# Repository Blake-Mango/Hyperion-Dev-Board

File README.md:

# Hyperion-Dev-Board

s a simple dev board that I made for Hack Club Blueprint. It has everything that I would want on a dev board—lots of GPIOs, plenty of grounds, and some other useful features (listed below). This was a fun and pretty easy project to make once I started to understand what I needed to do. It ended up being foundational to my ability to design PCBs, and it showed me how much I enjoy this kind of work. I hope I’ll be able to make even more dev boards later in life, and I’m definitely planning to try some other PCB ideas on Blueprint soon.

# Features
1. The RP2040 is the brain of this project handling all of the processing
2. this uses the W25Q16JVZPIQ with a whopping 16-Megabit flash menmory
3. Usbc this is just a normal USB-C Receptical to send data and also power 
4. one pin for 5v power and another pin for 3v power 
5. 9 pins for ground to make it easy to ground everything you need to 
6. this board comes wih 29 gpio pins 4 of which are dual use for analog inputs (ADC pins)
7. also on this board is an led to make it easy to check if the board is powered on od if there any any problems also to help debug or even program
8. and finaly a button to enter into BOOTSEL mode so you can program you board.

# schematic

# PCB Layout
### Front:

### Back:

# Heres what it looks like when made

# Demo
here is a short code that was made to just rotate the color of the onboard neopixel led

https://github.com/user-attachments/assets/beb6644e-a9f9-4d21-ad0d-ccec5cd91aba

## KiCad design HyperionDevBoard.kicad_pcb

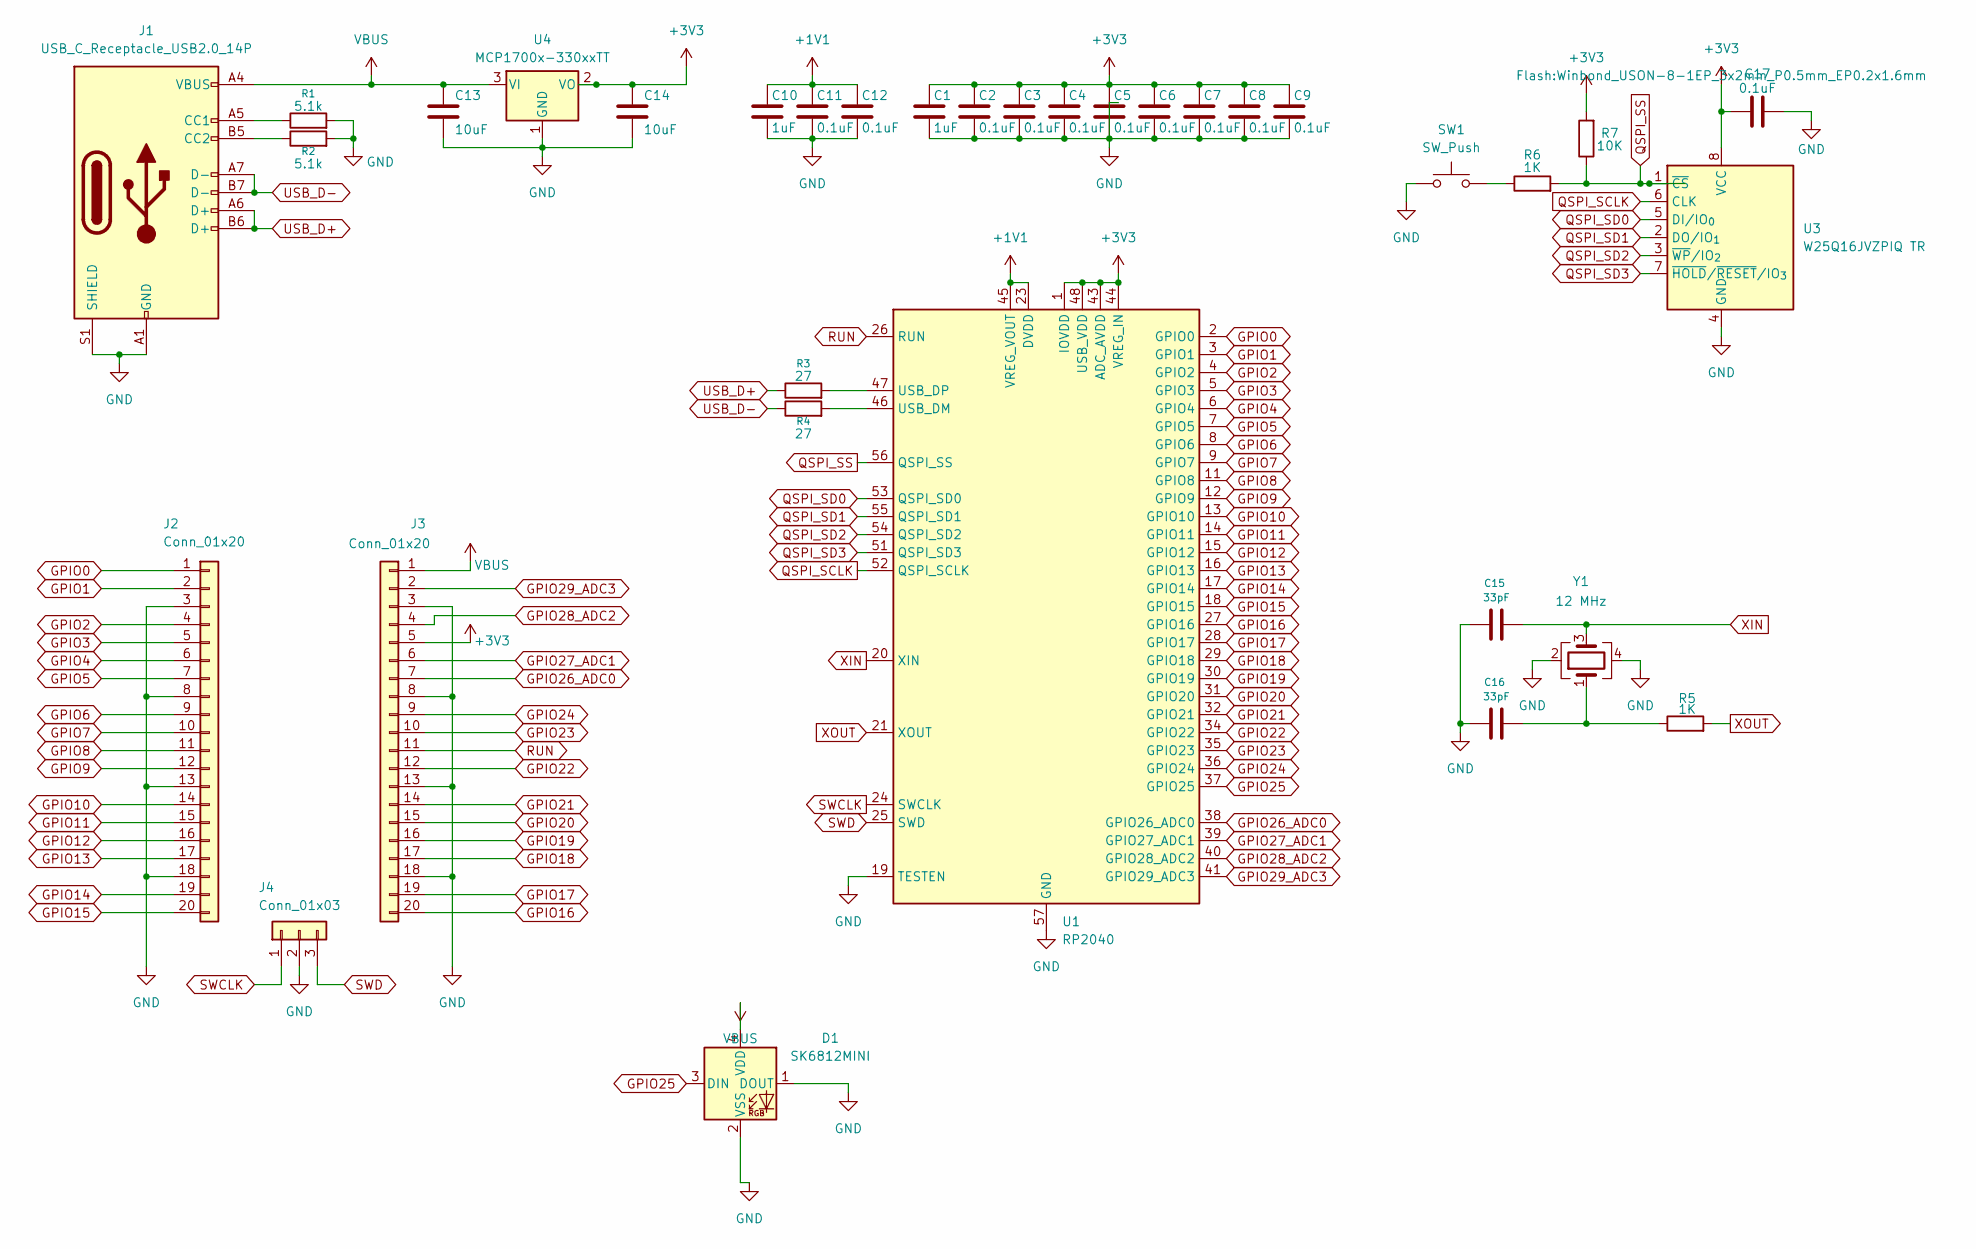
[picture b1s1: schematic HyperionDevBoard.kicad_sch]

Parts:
C1, C10: 1uF; C_0402_1005Metric
C2, C3, C4, C5, C6, C7, C8, C9, C11, C12, C17: 0.1uF; C_0402_1005Metric
C13, C14: 10uF; C_0603_1608Metric
C15, C16: 33pF; C_0402_1005Metric
D1: SK6812MINI; MX_SK6812MINI-E
J1: USB_C_Receptacle_USB2.0_14P; USB_C_Receptacle_HRO_TYPE-C-31-M-12
J2, J3: Conn_01x20; PinHeader_1x20_P2.54mm_Vertical
J4: Conn_01x03; PinHeader_1x03_P2.54mm_Vertical
R1, R2: 5.1k; R_0402_1005Metric
R3, R4: 27; R_0402_1005Metric
R5, R6: 1K; R_0402_1005Metric
R7: 10K; R_0402_1005Metric
SW1: SW_Push; SW_Push_SPST_NO_Alps_SKRK
U1: RP2040; QFN-56-1EP_7x7mm_P0.4mm_EP3.2x3.2mm
U3: W25Q16JVZPIQ TR; Winbond_USON-8-1EP_3x2mm_P0.5mm_EP0.2x1.6mm
U4: MCP1700x-330xxTT; SOT-23
Y1: 12 MHz; Crystal_SMD_3225-4Pin_3.2x2.5mm

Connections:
+1V1: C10.1, C11.1, C12.1, U1.23 (DVDD), U1.45 (VREG_VOUT), U1.50 (DVDD)
+3V3: C1.1, C2.1, C3.1, C4.1, C5.1, C6.1, C7.1, C8.1, C9.1, C14.1, C17.1, J3.5, R7.2, U1.1 (IOVDD), U1.10 (IOVDD), U1.22 (IOVDD), U1.33 (IOVDD), U1.42 (IOVDD), U1.43 (ADC_AVDD), U1.44 (VREG_IN), U1.48 (USB_VDD), U1.49 (IOVDD), U3.8 (VCC), U4.2 (VO)
GND: C1.2, C2.2, C3.2, C4.2, C5.2, C6.2, C7.2, C8.2, C9.2, C10.2, C11.2, C12.2, C13.2, C14.2, C15.1, C16.1, C17.2, D1.1 (DOUT), D1.2 (VSS), J1.A1 (GND), J1.A12 (GND), J1.B1 (GND), J1.B12 (GND), J1.S1 (SHIELD), J2.3, J2.8, J2.13, J2.18, J3.3, J3.8, J3.13, J3.18, J4.2, R1.2, R2.2, SW1.1, U1.19 (TESTEN), U1.57 (GND), U3.4 (GND), U4.1 (GND), Y1.2, Y1.4
GPIO0: J2.1, U1.2 (GPIO0)
GPIO1: J2.2, U1.3 (GPIO1)
GPIO2: J2.4, U1.4 (GPIO2)
GPIO3: J2.5, U1.5 (GPIO3)
GPIO4: J2.6, U1.6 (GPIO4)
GPIO5: J2.7, U1.7 (GPIO5)
GPIO6: J2.9, U1.8 (GPIO6)
GPIO7: J2.10, U1.9 (GPIO7)
GPIO8: J2.11, U1.11 (GPIO8)
GPIO9: J2.12, U1.12 (GPIO9)
GPIO10: J2.14, U1.13 (GPIO10)
GPIO11: J2.15, U1.14 (GPIO11)
GPIO12: J2.16, U1.15 (GPIO12)
GPIO13: J2.17, U1.16 (GPIO13)
GPIO14: J2.19, U1.17 (GPIO14)
GPIO15: J2.20, U1.18 (GPIO15)
GPIO16: J3.20, U1.27 (GPIO16)
GPIO17: J3.19, U1.28 (GPIO17)
GPIO18: J3.17, U1.29 (GPIO18)
GPIO19: J3.16, U1.30 (GPIO19)
GPIO20: J3.15, U1.31 (GPIO20)
GPIO21: J3.14, U1.32 (GPIO21)
GPIO22: J3.12, U1.34 (GPIO22)
GPIO23: J3.10, U1.35 (GPIO23)
GPIO24: J3.9, U1.36 (GPIO24)
GPIO25: D1.3 (DIN), U1.37 (GPIO25)
GPIO26_ADC0: J3.7, U1.38 (GPIO26_ADC0)
GPIO27_ADC1: J3.6, U1.39 (GPIO27_ADC1)
GPIO28_ADC2: J3.4, U1.40 (GPIO28_ADC2)
GPIO29_ADC3: J3.2, U1.41 (GPIO29_ADC3)
unnamed: C16.2, R5.1, Y1.1
unnamed: J1.A5 (CC1), R1.1
unnamed: J1.B5 (CC2), R2.1
unnamed: R6.1, SW1.2
unnamed: R4.2, U1.46 (USB_DM)
unnamed: R3.2, U1.47 (USB_DP)
QSPI_SCLK: U1.52 (QSPI_SCLK), U3.6 (CLK)
QSPI_SD0: U1.53 (QSPI_SD0), U3.5 (DI/IO_{0})
QSPI_SD1: U1.55 (QSPI_SD1), U3.2 (DO/IO_{1})
QSPI_SD2: U1.54 (QSPI_SD2), U3.3 (~WP/IO_{2})
QSPI_SD3: U1.51 (QSPI_SD3), U3.7 (~HOLD/~RESET/IO_{3})
QSPI_SS: R6.2, R7.1, U1.56 (QSPI_SS), U3.1 (~CS)
RUN: J3.11, U1.26 (RUN)
SWCLK: J4.1, U1.24 (SWCLK)
SWD: J4.3, U1.25 (SWD)
USB_D+: J1.A6 (D+), J1.B6 (D+), R3.1
USB_D-: J1.A7 (D-), J1.B7 (D-), R4.1
VBUS: C13.1, D1.4 (VDD), J1.A4 (VBUS), J1.A9 (VBUS), J1.B4 (VBUS), J1.B9 (VBUS), J3.1, U4.3 (VI)
XIN: C15.2, U1.20 (XIN), Y1.3
XOUT: R5.2, U1.21 (XOUT)

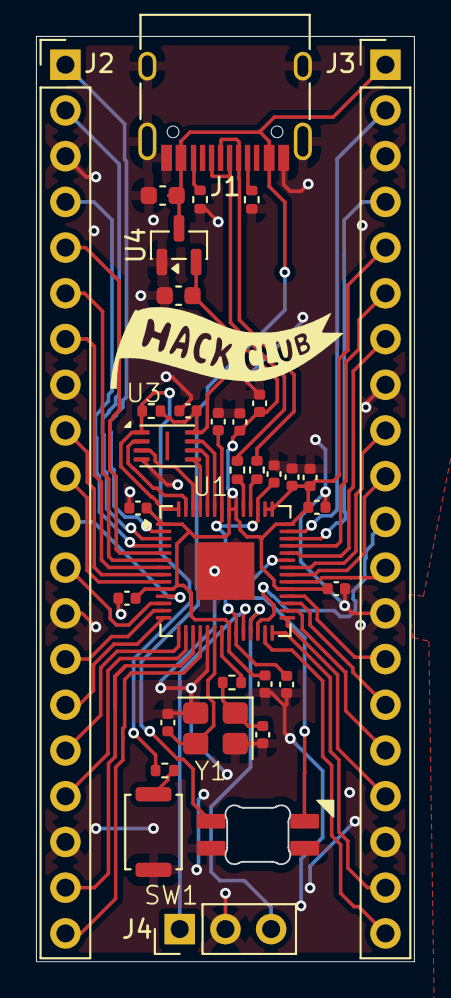
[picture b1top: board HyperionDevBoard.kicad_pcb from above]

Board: 2 copper layers, 21.0 x 51.4 mm, 34 parts (1 on the bottom side), 53 nets.

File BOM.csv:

Number,Type,footprint,Quantity,Quantity,Supplier,cost
"C3,C4,C11,C9,C2,C7,C6,C5,C8,C12,C17",0.1uF,C_0402_1005Metric,"CL05B104KO5NNNCC1525

100nF 16V X7R ±10% 0402 Multilayer Ceramic Capacitors MLCC - SMD/SMT ROHS",32,JLCPCB,$0.04
"C10,C1",1uF,C_0402_1005Metric,"CL05A105KA5NQNCC52923

1uF 25V X5R ±10% 0402 Multilayer Ceramic Capacitors MLCC - SMD/SMT ROHS",20,JLCPCB,$0.06
"C14,C13",10uF,C_0603_1608Metric,"CL10A106KP8NNNCC19702

10V 10uF X5R ±10% 0603 Multilayer Ceramic Capacitors MLCC - SMD/SMT ROHS",20,JLCPCB,$0.11
"C16,C15",33pF,C_0402_1005Metric,"0402CG330J500NTC1562

33pF 50V C0G ±5% 0402 Multilayer Ceramic Capacitors MLCC - SMD/SMT ROHS",20,JLCPCB,$0.02
D1,SK6812MINI,LED_SK6812MINI_PLCC4_3.5x3.5mm_P1.75mm,"SK6812MINI-EC5149201

-40℃~+85℃ 0.6mA 1.78mm 120° 1kHz 2.8mm 2000V 3.2mm 3.7V~5.5V 800Kbit/s G:815mcd~1275mcd R:620nm~625nm Semi-transparent lens SMD RGB LEDs(Built-in IC) ROHS",5,JLCPCB,$0.41
J1,USB_C_Receptacle_USB2.0_14P,USB_C_Receptacle_HRO_TYPE-C-31-M-12,"TYPE-C-31-M-12C165948

1 16P 5A Female Type-C SMD USB Connectors ROHS",2,JLCPCB,$0.34
"J3,J2",Conn_01x20,PinHeader_1x20_P2.54mm_Vertical,"2.54-1*20P直针C50981

-40℃~+105℃ 1 1x20P 2.54mm 20P 3A Black Brass Pin Header Through Hole Plugin,P=2.54mm Pin Headers ROHS",0,JLCPCB,$0.00
J4,Conn_01x03,PinHeader_1x03_P2.54mm_Vertical,"1.27-1*3P针C24980

-55℃~+105℃ 1 1.27mm 1mm 1x3P 2.3mm 3A 3P 3mm Black Brass Pin Header Through Hole Plugin,P=1.27mm Pin Headers ROHS",0,JLCPCB,$0.00
"R1,R2",5.1k,R_0402_1005Metric,"0402WGF5101TCEC25905

-55℃~+155℃ 5.1kΩ 50V 62.5mW Thick Film Resistor ±1% ±100ppm/℃ 0402 Chip Resistor - Surface Mount ROHS",20,JLCPCB,$0.01
"R3,R4",27,R_0402_1005Metric,"0402WGF270JTCEC25100

-55℃~+155℃ 27Ω 50V 62.5mW Thick Film Resistor ±1% ±100ppm/℃ 0402 Chip Resistor - Surface Mount ROHS",20,JLCPCB,$0.01
"R6,R5",1K,R_0402_1005Metric,"0402WGF1001TCEC11702

-55℃~+155℃ 1kΩ 50V 62.5mW Thick Film Resistor ±1% ±100ppm/℃ 0402 Chip Resistor - Surface Mount ROHS",20,JLCPCB,$0.01
R7,10K,R_0402_1005Metric,"0402WGF1002TCEC25744

-55℃~+155℃ 10kΩ 50V 62.5mW Thick Film Resistor ±1% ±100ppm/℃ 0402 Chip Resistor - Surface Mount ROHS",20,JLCPCB,$0.01
SW1,SW_Push,SW_Push_SPST_NO_Alps_SKRK,"TS-1088-AR02016C720477

-30℃~+80℃ 1.6N 100,000 Cycles 12V 2mm 3mm 4mm 50mA Black Round Button SMD(SMT) Tab SPST Surface Mount,Vertical Without Bracket SMD,4x3mm Tactile Switches ROHS",6,JLCPCB,$0.26
U1,RP2040,QFN-56-1EP_7x7mm_P0.4mm_EP3.2x3.2mm,"RP2040C2040

12bit 133MHz 30 LQFN-56(7x7) Microcontrollers (MCU/MPU/SOC) ROHS",2,JLCPCB,$1.83
U3,W25Q16JVZPIQTR,Winbond_USON-8-1EP_3x2mm_P0.5mm_EP0.2x1.6mm,"W25Q16JVUXIQC2843335

-40℃~+85℃ 100,000 Cycles 10uA 133MHz 16Mbit 2.7V~3.6V 20 Years 3ms SPI USON-8-EP(2x3) NOR FLASH ROHS",2,JLCPCB,$1.17
U4,MCP1700x-330xxTT,SOT-23,"MCP1700T-3302E/TTC39051

-40℃~+125℃@(Tj) 1 1.6uA 178mV@(250mA) 250mA 3.3V 44dB@(100Hz) 6V Fixed Over Temperature Protection Positive SOT-23 Voltage Regulators - Linear, Low Drop Out (LDO) Regulators ROHS",5,JLCPCB,$1.97
Y1,12MHz,Crystal_SMD_3225-4Pin_3.2x2.5mm,"X322512MSB4SIC9002

-40℃~+85℃ 12MHz 20pF Crystal Oscillator ±10ppm ±20ppm SMD3225-4P Crystals ROHS",6,JLCPCB,$0.39

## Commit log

2025-12-06 Enhance README with images and project details
    Added images and additional context about the project.
2025-12-07 Revise README with project overview and features
    Updated the README to provide a clearer description of the Hyperion Dev Board and its features.
2025-12-07 Revise README for clarity and add images
    Corrected grammar and improved clarity in the project description. Added a new section for images.
2025-12-07 Add PCB Layout section with images
    Added PCB layout images for front and back views.
2025-12-07 Fix BOM.csv formatting and add missing entries
2026-01-17 Update README with demo link for neopixel LED
    Added a link to a demo for color rotation of neopixel LED.
